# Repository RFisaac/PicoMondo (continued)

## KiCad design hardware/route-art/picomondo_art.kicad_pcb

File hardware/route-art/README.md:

# Route art

Decorative silkscreen idea from the v1 spec (§6.4): lines from the chip, through each ring LED, out to its EdgeLock contact, routed on one layer so nothing crosses. Decorative only; it does not follow the real copper.

- `picomondo_art.kicad_pro` / `picomondo_art.kicad_pcb`: art-only board (outline, LED ring and connector positions as graphics; no footprints).
- `picomondo_art_routed.kicad_pcb`: the same board after single-layer autorouting.
- `picomondo_art_routed_FCu.svg`: F.Cu exported from the routed board, ready to finish in a vector editor.
- `PicoMondo_v1_route_art.svg`, `PicoMondo_v1_board_art.vectorcraft`: the finished artwork (VectorCraft source and SVG export).

Not yet applied to the real board.

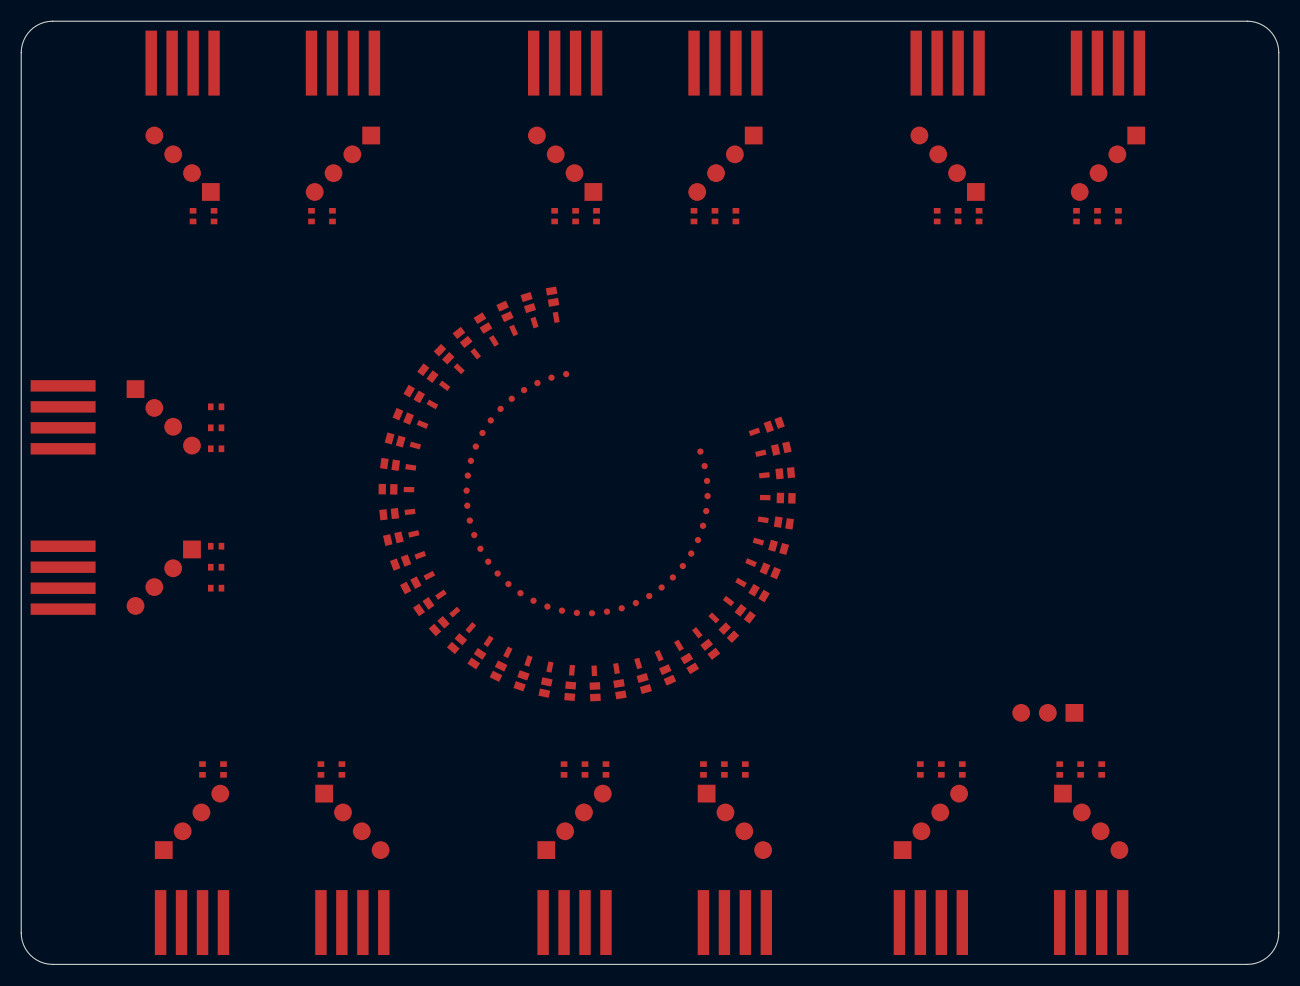
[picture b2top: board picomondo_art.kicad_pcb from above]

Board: 4 copper layers, 120.0 x 90.0 mm, 311 parts (0 on the bottom side), 80 nets, no tracks yet.

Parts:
D0, D1, D2, D3, D4, D5, D6, D7, D8, D9, D10, D11, D16, D17, D18, D19, D20, D21, D26, D27, D28, D29, D30, D31, D32, D33, D34, D35, D36, D37, D38, D39, D40, D41, D42, D43, D44, D45, D46, D47: LED
EL1.1, EL1.2, EL1.3, EL1.4, EL1.5, EL1.6, EL1.7, EL1.8, EL2.1, EL2.2, EL2.3, EL2.4, EL2.5, EL2.6, EL2.7, EL2.8, EL3.1, EL3.2, EL3.3, EL3.4, EL3.5, EL3.6, EL3.7, EL3.8, EL4.1, EL4.2, EL4.3, EL4.4, EL4.5, EL4.6, EL4.7, EL4.8, EL5.1, EL5.2, EL5.3, EL5.4, EL5.5, EL5.6, EL5.7, EL5.8, EL6.1, EL6.2, EL6.3, EL6.4, EL6.5, EL6.6, EL6.7, EL6.8, EL7.1, EL7.2, EL7.3, EL7.4, EL7.5, EL7.6, EL7.7, EL7.8: contact
EL1.H1, EL1.H2, EL1.H3, EL1.H4, EL1.H5, EL1.H6, EL1.H7, EL1.H8, EL2.H1, EL2.H2, EL2.H3, EL2.H4, EL2.H5, EL2.H6, EL2.H7, EL2.H8, EL3.H1, EL3.H2, EL3.H3, EL3.H4, EL3.H5, EL3.H6, EL3.H7, EL3.H8, EL4.H1, EL4.H2, EL4.H3, EL4.H4, EL4.H5, EL4.H6, EL4.H7, EL4.H8, EL5.H1, EL5.H2, EL5.H3, EL5.H4, EL5.H5, EL5.H6, EL5.H7, EL5.H8, EL6.H1, EL6.H2, EL6.H3, EL6.H4, EL6.H5, EL6.H6, EL6.H7, EL6.H8, EL7.H1, EL7.H2, EL7.H3, EL7.H4, EL7.H5, EL7.H6, EL7.H7, EL7.H8: hole
NPX.H1, NPX.H2, NPX.H3: hole
R0, R1, R2, R3, R4, R5, R6, R7, R8, R9, R10, R11, R16, R17, R18, R19, R20, R21, R26, R27, R28, R29, R30, R31, R32, R33, R34, R35, R36, R37, R38, R39, R40, R41, R42, R43, R44, R45, R46, R47: 470R
R100_0, R100_1, R100_2, R100_3, R100_4, R100_5, R100_6, R100_7, R100_8, R100_9, R100_10, R100_11, R100_16, R100_17, R100_18, R100_19, R100_20, R100_21, R100_26, R100_27, R100_28, R100_29, R100_30, R100_31, R100_32, R100_33, R100_36, R100_37, R100_38, R100_39, R100_40, R100_41, R100_42, R100_43, R100_44, R100_45, R100_46, R100_47, R100b_0, R100b_1, R100b_2, R100b_3, R100b_4, R100b_5, R100b_6, R100b_7, R100b_8, R100b_9, R100b_10, R100b_11, R100b_16, R100b_17, R100b_18, R100b_19, R100b_20, R100b_21, R100b_26, R100b_27, R100b_28, R100b_29, R100b_30, R100b_31, R100b_32, R100b_33, R100b_36, R100b_37, R100b_38, R100b_39, R100b_40, R100b_41, R100b_42, R100b_43, R100b_44, R100b_45, R100b_46, R100b_47: 100R
S0, S1, S2, S3, S4, S5, S6, S7, S8, S9, S10, S11, S16, S17, S18, S19, S20, S21, S26, S27, S28, S29, S30, S31, S32, S33, S34, S35, S36, S37, S38, S39, S40, S41, S42, S43, S44, S45, S46, S47: chip_stub

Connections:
GPIO0: D0.2, EL2.4.1, EL2.H4.1, R100_0.1, R100b_0.1
GPIO0_in: D0.1, R0.1, S0.1
GPIO1: D1.2, EL2.5.1, EL2.H5.1, R100_1.1, R100b_1.1
GPIO1_in: D1.1, R1.1, S1.1
GPIO2: D2.2, EL2.6.1, EL2.H6.1, R100_2.1, R100b_2.1
GPIO2_in: D2.1, R2.1, S2.1
GPIO3: D3.2, EL2.7.1, EL2.H7.1, R100_3.1, R100b_3.1
GPIO3_in: D3.1, R3.1, S3.1
GPIO4: D4.2, EL1.3.1, EL1.H3.1, R100_4.1, R100b_4.1
GPIO4_in: D4.1, R4.1, S4.1
GPIO5: D5.2, EL1.4.1, EL1.H4.1, R100_5.1, R100b_5.1
GPIO5_in: D5.1, R5.1, S5.1
GPIO6: D6.2, EL1.5.1, EL1.H5.1, R100_6.1, R100b_6.1
GPIO6_in: D6.1, R6.1, S6.1
GPIO7: D7.2, EL1.6.1, EL1.H6.1, R100_7.1, R100b_7.1
GPIO7_in: D7.1, R7.1, S7.1
GPIO8: D8.2, EL7.2.1, EL7.H2.1, R100_8.1, R100b_8.1
GPIO8_in: D8.1, R8.1, S8.1
GPIO9: D9.2, EL7.3.1, EL7.H3.1, R100_9.1, R100b_9.1
GPIO9_in: D9.1, R9.1, S9.1
GPIO10: D10.2, EL7.4.1, EL7.H4.1, R100_10.1, R100b_10.1
GPIO10_in: D10.1, R10.1, S10.1
GPIO11: D11.2, EL7.5.1, EL7.H5.1, R100_11.1, R100b_11.1
GPIO11_in: D11.1, R11.1, S11.1
GPIO16: D16.2, EL7.6.1, EL7.H6.1, R100_16.1, R100b_16.1
GPIO16_in: D16.1, R16.1, S16.1
GPIO17: D17.2, EL7.7.1, EL7.H7.1, R100_17.1, R100b_17.1
GPIO17_in: D17.1, R17.1, S17.1
GPIO18: D18.2, EL4.3.1, EL4.H3.1, R100_18.1, R100b_18.1
GPIO18_in: D18.1, R18.1, S18.1
GPIO19: D19.2, EL4.4.1, EL4.H4.1, R100_19.1, R100b_19.1
GPIO19_in: D19.1, R19.1, S19.1
GPIO20: D20.2, EL4.5.1, EL4.H5.1, R100_20.1, R100b_20.1
GPIO20_in: D20.1, R20.1, S20.1
GPIO21: D21.2, EL4.6.1, EL4.H6.1, R100_21.1, R100b_21.1
GPIO21_in: D21.1, R21.1, S21.1
GPIO26: D26.2, EL5.4.1, EL5.H4.1, R100_26.1, R100b_26.1
GPIO26_in: D26.1, R26.1, S26.1
GPIO27: D27.2, EL5.5.1, EL5.H5.1, R100_27.1, R100b_27.1
GPIO27_in: D27.1, R27.1, S27.1
GPIO28: D28.2, EL5.6.1, EL5.H6.1, R100_28.1, R100b_28.1
GPIO28_in: D28.1, R28.1, S28.1
GPIO29: D29.2, EL5.7.1, EL5.H7.1, R100_29.1, R100b_29.1
GPIO29_in: D29.1, R29.1, S29.1
GPIO30: D30.2, EL6.4.1, EL6.H4.1, R100_30.1, R100b_30.1
GPIO30_in: D30.1, R30.1, S30.1
GPIO31: D31.2, EL6.5.1, EL6.H5.1, R100_31.1, R100b_31.1
GPIO31_in: D31.1, R31.1, S31.1
GPIO32: D32.2, EL6.6.1, EL6.H6.1, R100_32.1, R100b_32.1
GPIO32_in: D32.1, R32.1, S32.1
GPIO33: D33.2, EL6.7.1, EL6.H7.1, R100_33.1, R100b_33.1
GPIO33_in: D33.1, R33.1, S33.1
GPIO34: D34.2, NPX.H1.1
GPIO34_in: D34.1, R34.1, S34.1
GPIO35: D35.2, NPX.H2.1
GPIO35_in: D35.1, R35.1, S35.1
GPIO36: D36.2, EL3.4.1, EL3.H4.1, R100_36.1, R100b_36.1
GPIO36_in: D36.1, R36.1, S36.1
GPIO37: D37.2, EL3.5.1, EL3.H5.1, R100_37.1, R100b_37.1
GPIO37_in: D37.1, R37.1, S37.1
GPIO38: D38.2, EL3.6.1, EL3.H6.1, R100_38.1, R100b_38.1
GPIO38_in: D38.1, R38.1, S38.1
GPIO39: D39.2, EL3.7.1, EL3.H7.1, R100_39.1, R100b_39.1
GPIO39_in: D39.1, R39.1, S39.1
GPIO40: D40.2, EL5.2.1, EL5.H2.1, R100_40.1, R100b_40.1
GPIO40_in: D40.1, R40.1, S40.1
GPIO41: D41.2, EL5.3.1, EL5.H3.1, R100_41.1, R100b_41.1
GPIO41_in: D41.1, R41.1, S41.1
GPIO42: D42.2, EL6.2.1, EL6.H2.1, R100_42.1, R100b_42.1
GPIO42_in: D42.1, R42.1, S42.1
GPIO43: D43.2, EL6.3.1, EL6.H3.1, R100_43.1, R100b_43.1
GPIO43_in: D43.1, R43.1, S43.1
GPIO44: D44.2, EL3.2.1, EL3.H2.1, R100_44.1, R100b_44.1
GPIO44_in: D44.1, R44.1, S44.1
GPIO45: D45.2, EL3.3.1, EL3.H3.1, R100_45.1, R100b_45.1
GPIO45_in: D45.1, R45.1, S45.1
GPIO46: D46.2, EL2.2.1, EL2.H2.1, R100_46.1, R100b_46.1
GPIO46_in: D46.1, R46.1, S46.1
GPIO47: D47.2, EL2.3.1, EL2.H3.1, R100_47.1, R100b_47.1
GPIO47_in: D47.1, R47.1, S47.1
